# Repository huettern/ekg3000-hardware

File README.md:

EKG-3000 Hardware design
========================

Designed using CADSoft Eagle

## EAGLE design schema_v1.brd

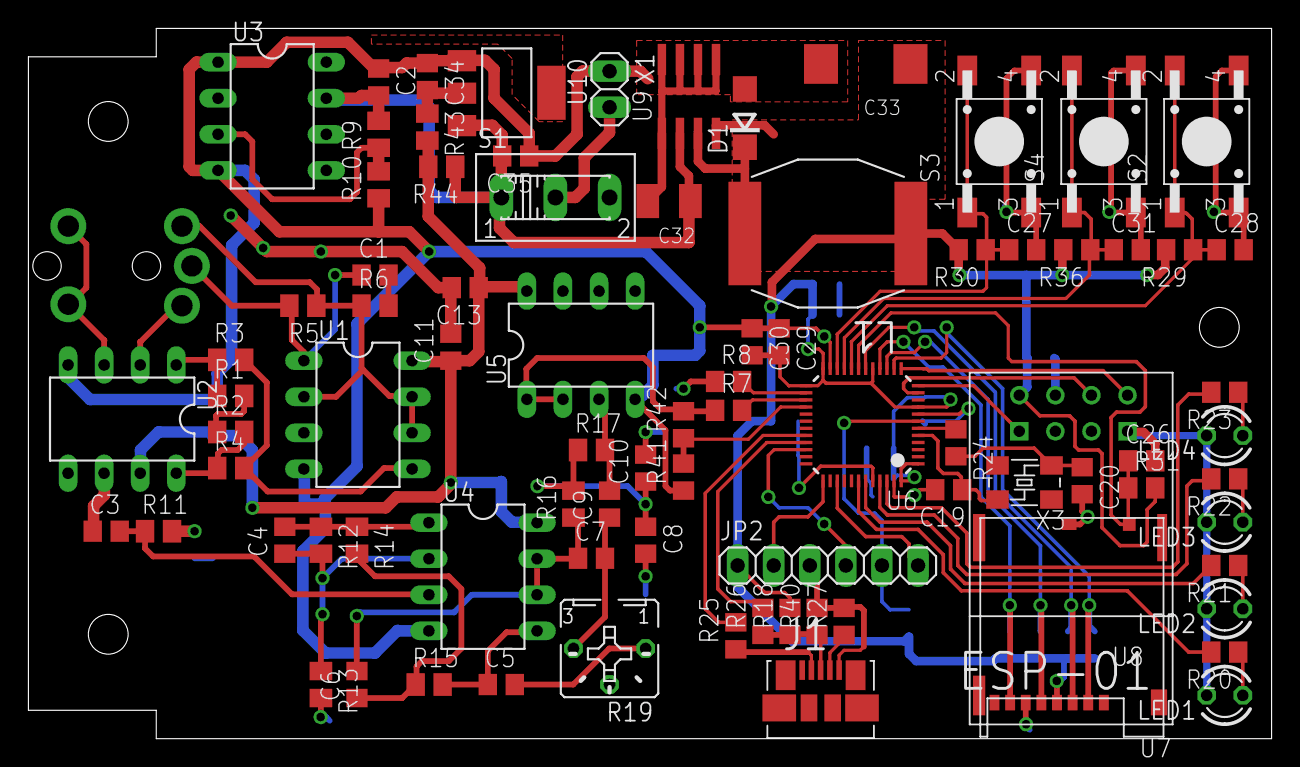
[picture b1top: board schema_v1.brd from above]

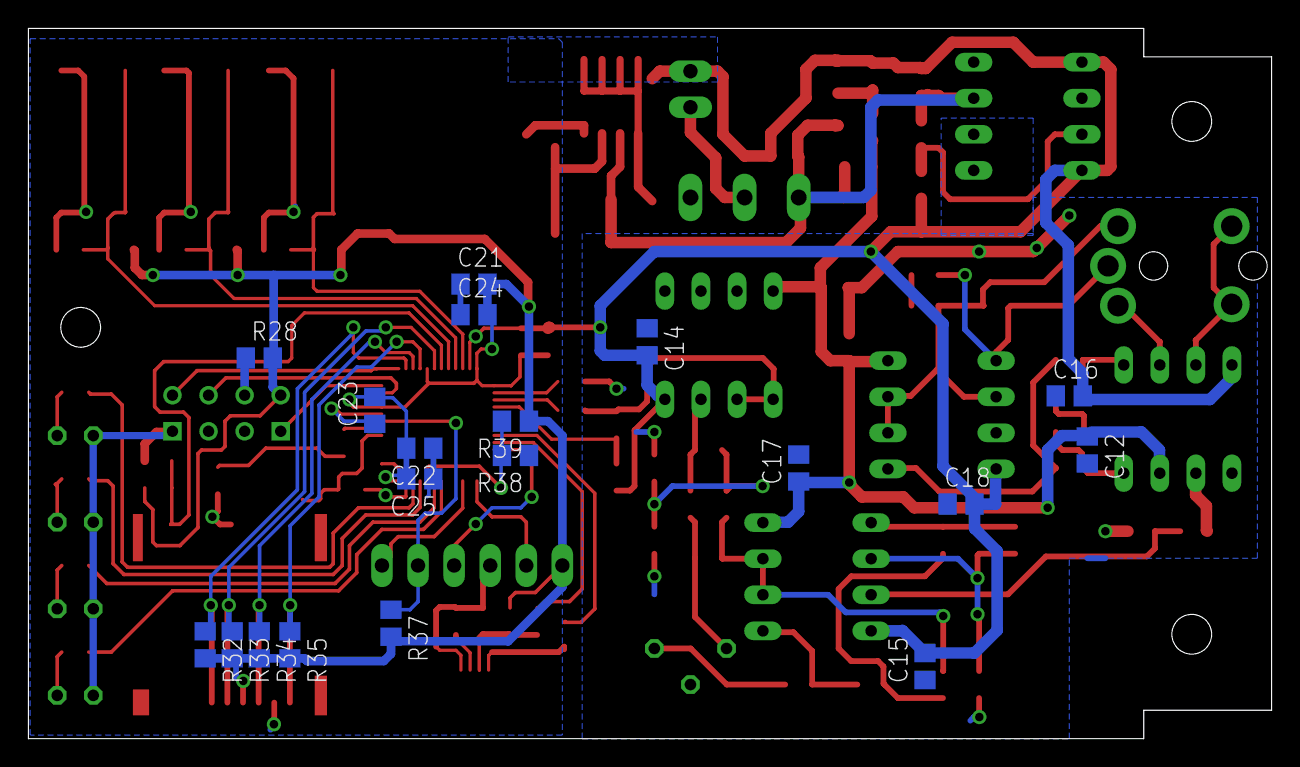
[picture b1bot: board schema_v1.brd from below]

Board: 2 copper layers, 87.5 x 50.0 mm, 104 parts (19 on the bottom side), 65 nets.

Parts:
C1, C4, C5, C6, C30: 10n; C0805
C2, C3, C29, C34, C35: 1u; C0805
C7, C8, C9, C10: 47n; C0805
C11, C12, C13, C14, C15, C16, C17, C18, C21, C22, C23, C26, C27, C28, C31: 100n; C0805
C19, C20: 22p; C0805
C24, C25: 4.7u; C0805
C32: 15u; SMC_B
C33: 220u; SMC_E
D1: DO214AC
J1: MOLEX_47346-0001
JP2: 1X06
L1: 68µH; INDM1410X600N
LED1, LED2, LED3, LED4: LED3MM
R1, R2: 3k; M0805
R3, R4: 30k; M0805
R5, R11: 1M; M0805
R6: 12k; M0805
R7, R8: 0; R0805
R9, R10, R15: 100k; M0805
R12, R16, R17: 68k; M0805
R13: 1k; M0805
R14: 39k; M0805
R18, R40: 1.5k; R0805
R19: B25P
R20, R21, R22, R23: R0805
R24: 0E; R0805
R25, R26: 22E; R0805
R27: 100k; R0805
R28, R29, R30, R31, R32, R33, R34, R35, R36, R37, R38, R39: 10k; R0805
R41: 3.3k; R0805
R42: 6.8k; R0805
R43, R44: 0; M0805
S1: 255SB
S2, S3, S4: TASTER-9314_SMD
U1, U4, U5: LT1112N; DIL08
U2: LT1167A; DIL08
U3: BUF634PDIL08; DIL08
U6: STM32F373CCT6LQFP48-7X7; LQFP48-7X7
U7: ESP01
U8: MICROSD; SD-503398-003
U9: MIC4680-3.3YM; SOIC8
U10: REG1117; SOT223
X1: 1X02
X2: MJ2135; MJ-2135
X3: ABM3B; IQG5032B

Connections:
+3V3: C21.2, C22.2, C23.2, C24.2, C25.2, C29.2, C30.2, C33.+, JP2.1, L1.1, R18.2, R28.2, R29.2, R30.2, R31.2, R32.2, R33.2, R34.2, R35.2, R36.2, R37.2, R39.1, U6.1, U6.9, U6.17, U6.24, U6.25, U6.48, U7.VCC, U8.4, U9.4
/RST: JP2.5, R37.1, U6.7
ADC: R41.2, R42.1, U6.28
DRIVEN_LEG: C1.1, R5.2, U1.1, X2.P$1
EKG_SIGNAL: R7.1, R42.2, U5.1, U5.2
ESP_PD: U6.11, U7.CH_PD
ESP_RX: U6.12, U7.RX
ESP_TX: U6.13, U7.TX
LEDG: R20.2, U6.42
LEDM: R22.2, U6.45
LEDR: R23.2, U6.46
LEDW: R21.2, U6.43
unnamed: R1.1, R3.1, U2.1
unnamed: C8.1, C10.1, R16.2, R17.1
unnamed: R1.2, R2.1
unnamed: R7.2, U6.27
unnamed: R9.1, R10.2, U3.3
unnamed: C1.2, R6.2
unnamed: R8.2, U6.26
unnamed: U2.2, X2.P$3
unnamed: U2.3, X2.P$4, X2.P$5
unnamed: LED1.A, R20.1
unnamed: C3.1, U2.6
unnamed: C3.2, R11.1, U4.3
unnamed: R2.2, R4.1, U2.8
unnamed: LED2.A, R21.1
unnamed: C6.2, C7.1, R16.1, U4.6, U4.7
unnamed: C4.2, R12.1, R14.1, U4.1
unnamed: R3.2, R4.2, U1.5
unnamed: S1.2, X1.2
unnamed: C6.1, R14.2, R15.1
unnamed: C5.1, R15.2, U4.5
unnamed: LED3.A, R22.1
unnamed: C9.2, R17.2, U5.3
unnamed: C7.2, C9.1, R19.E
unnamed: LED4.A, R23.1
unnamed: J1.4, R27.1
unnamed: J1.3, R18.1, R26.1, R40.1
unnamed: J1.2, R25.1
unnamed: R28.1, U7.RST
unnamed: C20.1, R24.2, X3.1
unnamed: R38.2, R39.2, U6.44
unnamed: D1.C, L1.2, U9.3
unnamed: C34.2, R43.1, U10.2
unnamed: C4.1, R12.2, R13.1, U4.2
OSC_IN: C19.1, U6.5, X3.3
OSC_OUT: R24.1, U6.6
SD_MISO: R35.1, U6.16, U8.7
SD_MOSI: R33.1, U6.18, U8.3
SD_NSS: R32.1, U6.14, U8.2
SD_SCK: R34.1, U6.15, U8.5
SD_SWITCH: C26.1, R31.1, U6.19, U8.9
SHIELD: R5.1, R6.1, U1.2, U1.6, U1.7, X2.P$2
SWCLK: JP2.2, U6.37
SWDAT: JP2.4, U6.34
SWO: JP2.6, U6.39
T_START: C28.1, R29.1, S2.1, S2.2, U6.20
T_STARTLONG: C31.1, R36.1, S4.1, S4.2, U6.21
T_WPS: C27.1, R30.1, S3.1, S3.2, U6.22
USB_DM: R25.2, U6.32
USB_DP: R26.2, U6.33
V+: C11.1, C12.1, C13.1, C17.1, R43.2, R44.2, U1.8, U2.7, U4.8, U5.8
V-: C2.1, C14.2, C15.2, C16.2, C18.2, C19.2, C20.2, C21.1, C22.1, C23.1, C24.1, C25.1, C26.2, C27.2, C28.2, C29.1, C30.1, C31.2, C32.-, C33.-, C34.1, C35.1, D1.A, J1.5, JP2.3, LED1.K, LED2.K, LED3.K, LED4.K, R10.1, R27.2, R38.1, R40.2, R41.1, S2.3, S2.4, S3.3, S3.4, S4.3, S4.4, U1.4, U2.4, U3.1, U3.4, U4.4, U5.4, U6.8, U6.23, U6.47, U7.GND, U8.6, U8.10, U9.1, U9.5, U9.6, U9.7, U9.8, U10.1, X1.1
VBAT: C2.2, C32.+, C35.2, R9.2, R44.1, S1.1, U3.7, U9.2, U10.3
VGND: C5.2, C8.2, C10.2, C11.2, C12.2, C13.2, C14.1, C15.1, C16.1, C17.2, C18.1, R8.1, R11.2, R13.2, R19.A, U1.3, U2.5, U3.6, U5.5, U5.6

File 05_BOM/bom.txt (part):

Partlist

Exported from schema_v1.brd at 24/11/16 14:31

EAGLE Version 7.6.0 Copyright (c) 1988-2016 CadSoft

Assembly variant: 

Part     Value          Package               Library        Position (inch)       Orientation

C1       10n            C0805                 resistor       (1 1.3)               R0
C2       1u             C0805                 resistor       (1.5 1.8)             R270
C3       1u             C0805                 resistor       (0.2 0.6)             R0
C4       10n            C0805                 resistor       (0.75 0.55)           R90
C5       10n            C0805                 resistor       (1.35 0.15)           R0
C6       10n            C0805                 resistor       (0.95 0.15)           R90
C7       47n            C0805                 resistor       (1.6 0.5)             R0
C8       47n            C0805                 resistor       (1.75 0.55)           R270
C9       47n            C0805                 resistor       (1.65 0.65)           R90
C10      47n            C0805                 resistor       (1.75 0.75)           R90
C11      100n           C0805                 resistor       (1.2 1.15)            R180
C12      100n           C0805                 resistor       (0.55 0.8)            MR270
C13      100n           C0805                 resistor       (1.25 1.25)           R180
C14      100n           C0805                 resistor       (1.8 1.05)            MR270
C15      100n           C0805                 resistor       (1 0.2)               MR90
C16      100n           C0805                 resistor       (0.6 0.95)            MR0
C17      100n           C0805                 resistor       (1.35 0.75)           MR90
C18      100n           C0805                 resistor       (0.9 0.65)            MR0
C19      22p            C0805                 resistor       (2.59 0.69)           R180
C20      22p            C0805                 resistor       (2.96 0.715)          R270
C21      100n           C0805                 resistor       (2.25 1.26)           MR0
C22      100n           C0805                 resistor       (2.4 0.805)           MR180
C23      100n           C0805                 resistor       (2.525 0.91)          MR90
C24      4.7u           C0805                 resistor       (2.25 1.175)          MR0
C25      4.7u           C0805                 resistor       (2.4 0.72)            MR180
C26      100n           C0805                 resistor       (3.125 0.77)          R0
C27      100n           C0805                 resistor       (2.795 1.355)         R0
C28      100n           C0805                 resistor       (3.37 1.355)          R0
C29      1u             C0805                 resistor       (2.12 1.085)          R270
C30      10n            C0805                 resistor       (2.045 1.085)         R270
C31      100n           C0805                 resistor       (3.085 1.355)         R0
C32      15u            SMC_B                 rcl            (1.815 1.49)          R180
C33      220u           SMC_E                 rcl            (2.36 1.87)           R180
D1                      DO214AC               diode          (2.025 1.72)          R90
J1                      MOLEX_47346-0001      pro3E          (2.235 0.19)          R0
JP2                     1X06                  pinhead        (2.255 0.48)          R0
L1       68µH           INDM1410X600N         pro3E          (2.255 1.4)           R180
LED1                    LED3MM                led            (3.355 0.12)          R180
LED2                    LED3MM                led            (3.355 0.36)          R180
LED3                    LED3MM                led            (3.355 0.6)           R180
LED4                    LED3MM                led            (3.355 0.84)          R180
R1       3k             M0805                 resistor       (0.6 0.95)            R0
R2       3k             M0805                 resistor       (0.6 0.85)            R0
R3       30k            M0805                 resistor       (0.6 1.05)            R0
R4       30k            M0805                 resistor       (0.6 0.75)            R0
R5       1M             M0805                 resistor       (0.8 1.2)             R180
R6       12k            M0805                 resistor       (1 1.2)               R0
R7       100k           M0805                 resistor       (1.35 0.75)           R90
R8       100k           M0805                 resistor       (1.25 0.75)           R270
R9       100k           M0805                 resistor       (1.3 1.7)             R0
R10      100k           M0805                 resistor       (1.3 1.82)            R0
R11      1M             M0805                 resistor       (0.4 0.6)             R0
R12      68k            M0805                 resistor       (0.85 0.55)           R270
R13      1k             M0805                 resistor       (0.85 0.15)           R270
R14      39k            M0805                 resistor       (0.95 0.55)           R270
R15      100k           M0805                 resistor       (1.15 0.15)           R0
R16      68k            M0805                 resistor       (1.55 0.65)           R90
R17      68k            M0805                 resistor       (1.6 0.8)             R0
R18      1.5k           R0805                 resistor       (2.15 0.325)          R90
R19                     B25P                  pot            (1.65 0.25)           R180
R20                     R0805                 resistor       (3.355 0.24)          R180
R21                     R0805                 resistor       (3.355 0.48)          R180
R22                     R0805                 resistor       (3.355 0.72)          R180
R23                     R0805                 resistor       (3.355 0.96)          R180
R24      0E             R0805                 resistor       (2.61 0.82)           R270
R25      22E            R0805                 resistor       (2 0.285)             R90
R26      22E            R0805                 resistor       (2.075 0.325)         R90
R27      100k           R0805                 resistor       (2.3 0.325)           R90
R28      10k            R0805                 resistor       (2.845 1.055)         MR0
R29      10k            R0805                 resistor       (3.23 1.355)          R180
R30      10k            R0805                 resistor       (2.655 1.355)         R180
R31      10k            R0805                 resistor       (3.125 0.695)         R0
R32      10k            R0805                 resistor       (2.715 0.255)         MR270
R33      10k            R0805                 resistor       (2.805 0.255)         MR270
R34      10k            R0805                 resistor       (2.895 0.255)         MR270
R35      10k            R0805                 resistor       (2.985 0.255)         MR270
R36      10k            R0805                 resistor       (2.945 1.355)         R180
R37      10k            R0805                 resistor       (2.48 0.32)           MR270
R38      10k            R0805                 resistor       (2.135 0.785)         MR180
R39      10k            R0805                 resistor       (2.135 0.88)          MR180
R40      1.5k           R0805                 resistor       (2.225 0.325)         R90
R41      3.3k           R0805                 resistor       (1.85 1)              R90
R42      6.8k           R0805                 resistor       (1.85 1.15)           R90
S1                      255SB                 switch         (1.5 1.5)             R0
S2                      TASTER-9314_SMD       pro3E          (3.305 1.655)         R90
S3                      TASTER-9314_SMD       pro3E          (2.73 1.655)          R90
S4                      TASTER-9314_SMD       pro3E          (3.02 1.655)          R90
U$1      ABM3B          IQG5032B              pro3E          (2.8 0.71)            R180
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
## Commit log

2016-10-30 libary and schematic
2016-10-30 tutorial
2017-01-19 final files for prototype
2017-01-19 readme
2017-01-19 license
